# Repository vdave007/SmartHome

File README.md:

# SmartHome
Smart Home -hardware and backend

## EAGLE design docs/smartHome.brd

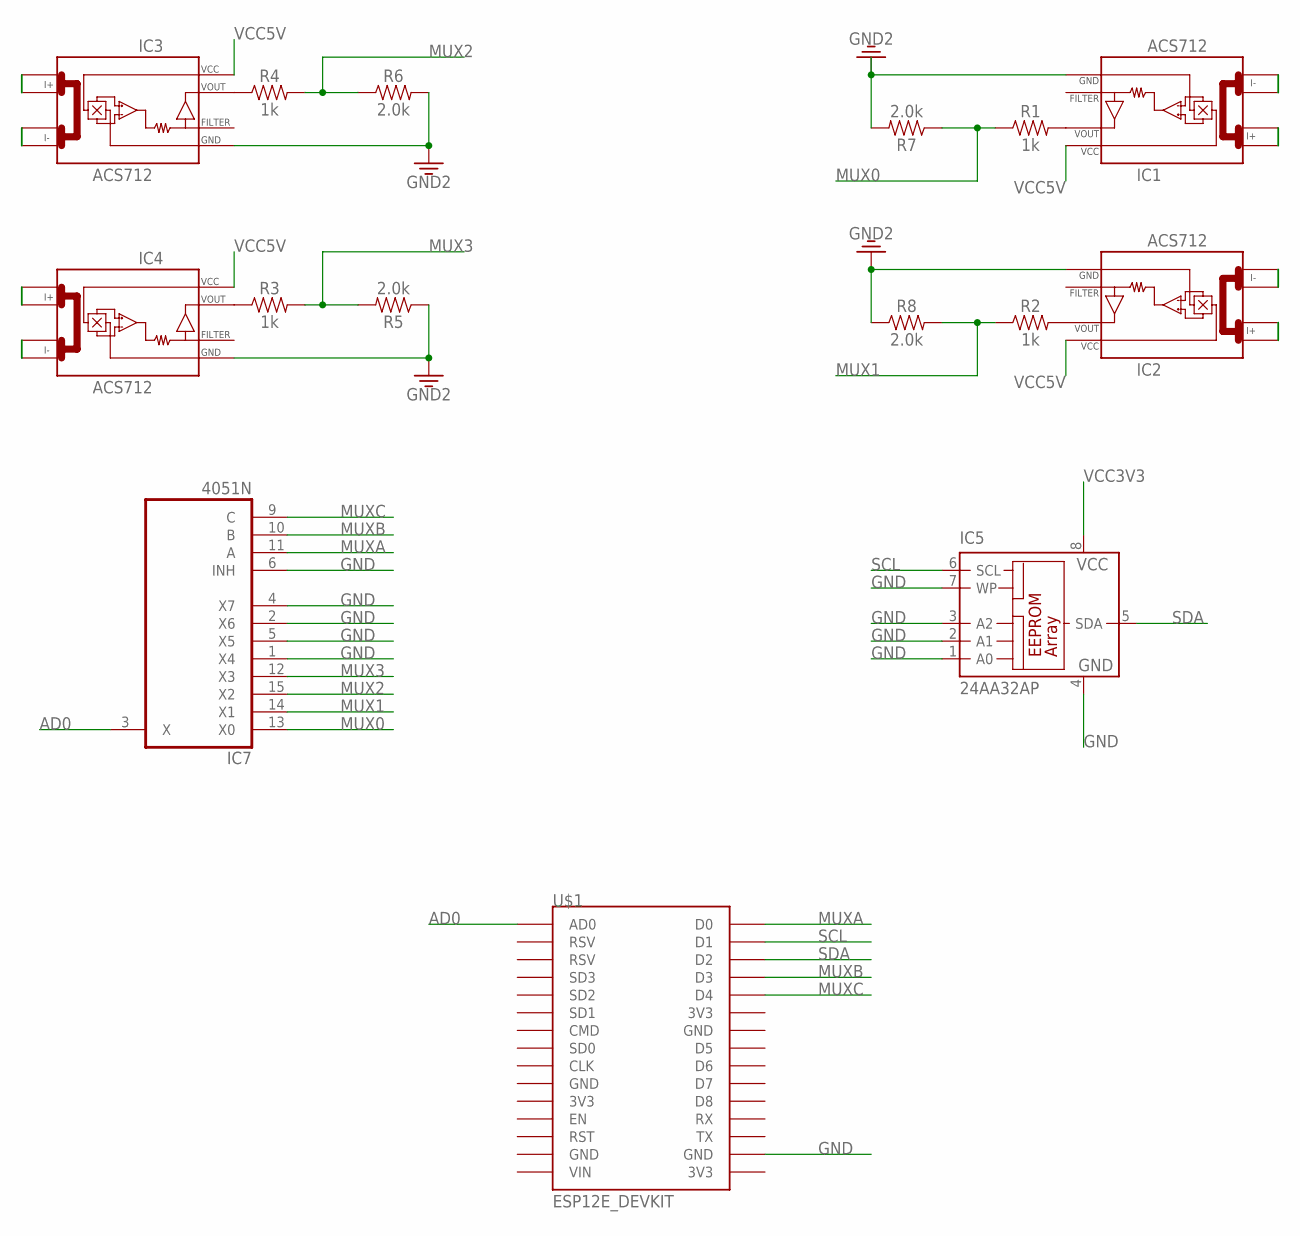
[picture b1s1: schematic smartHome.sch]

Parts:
IC1, IC2, IC3, IC4: ACS712; SO08
IC5: 24AA32AP; DIL8
IC7: 4051N; DIL16
R1, R2, R3, R4: 1k; AXIAL-0.3
R5, R6, R7, R8: 2.0k; 0603
U$1: ESP12E_DEVKIT

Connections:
AD0: IC7.3 (X), U$1.AD0
GND: IC1.5 (GND), IC2.5 (GND), IC3.5 (GND), IC4.5 (GND), IC5.1 (A0), IC5.2 (A1), IC5.3 (A2), IC5.4 (GND), IC5.7 (WP), IC7.1 (X4), IC7.2 (X6), IC7.4 (X7), IC7.5 (X5), IC7.6 (INH), IC7.8 (GND), R5.1, R6.2, R7.2, R8.1, U$1.GND@3 (GND)
MUX0: IC7.13 (X0), R1.P$1 (1), R7.1
MUX1: IC7.14 (X1), R2.P$1 (1), R8.2
MUX2: IC7.15 (X2), R4.P$2 (2), R6.1
MUX3: IC7.12 (X3), R3.P$2 (2), R5.2
MUXA: IC7.11 (A), U$1.D0
MUXB: IC7.10 (B), U$1.D3
MUXC: IC7.9 (C), U$1.D4
unnamed: IC1.7 (VOUT), R1.P$2 (2)
unnamed: IC2.7 (VOUT), R2.P$2 (2)
unnamed: IC3.7 (VOUT), R4.P$1 (1)
unnamed: IC4.7 (VOUT), R3.P$1 (1)
SCL: IC5.6 (SCL), U$1.D1
SDA: IC5.5 (SDA), U$1.D2
VCC: IC7.16 (VCC)
VCC3V3: IC5.8 (VCC)
VCC5V: IC1.8 (VCC), IC2.8 (VCC), IC3.8 (VCC), IC4.8 (VCC)
VEE: IC7.7 (VEE)

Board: 2 copper layers, 15 parts (0 on the bottom side), 16 nets, no tracks yet.

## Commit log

2017-01-04 Skeleton for the backend. Very primitive yet.
2017-01-04 Added mongoose implementation
2017-01-04 Added API for hardware to post his raw data
2017-02-07 Added communication: backend-hardware
2017-02-20 Corrected some errors so it works on cloud to
    *Added "use strict"
2017-02-20 Rewrote the code so now its more OOP and uses PlatformIO
2017-02-21 Added Acs712 and NetworkController classes
    * !Untested on device
2017-02-27 Added EEPROM class *UNTESTED!
2017-03-05 Tested on device!
2017-03-06 Corrected getACRMS function
2017-03-24 added backend for android
2017-03-24 it need to be int watt value
2017-03-25 Config store and new eeprom implementation... MUST FINISH
2017-03-26 Implemented some configstor, still needs changes.
2017-03-27 added original_value for fix the devicesetting bug
2017-04-01 mesages refactored to boolean
2017-04-02 Corrected EEPROM and now reports with good device ID
2017-04-02 Implemented ConfigStore Save
2017-04-03 Revolutionary measurement!
2017-04-10 Added Eagle-file for SmartHome+NodeMCU
2017-04-10 Rewrote to POST
2017-04-10 added body parser
2017-04-11 added socket
2017-04-11 notification sender
2017-04-17 Started implementing eepromInitializer with config page. Get method added to networkController
2017-05-15 Added support for WeMoS D1
2017-05-19 added socket for notification
2017-05-31 Added Docker support for the backend.
2017-06-01 Quickfix in docker file
2017-06-01 gethousesbyid method added
2017-06-02 Created the configpage for the device
    *Pin D5 must be pulled HIGH for the device to enter config-mode
    *When in config mode you access the device on the 192.168.4.1 IP
    *Wifi and backend can be configured here
2017-06-02 Small fix - changed saving method for backend ip
2017-06-03 Fixed eeprom configuration save issue
2017-06-03 Added custom structure that keeps the last X number of measured current on the given cID
2017-06-03 Modified docker-compose file so it will work on AWS
2017-06-03 Corrected typo
2017-06-03 Fixed Eeprom write if you get smaller string after bigger
2017-06-04 id type changed to string
2017-06-07 valuedelay added
2017-06-08 Quickfix for FirstRun
2017-06-08 added mailer for sending reset password mails
2017-06-24 added model for resetpassword to save in db
2017-06-25 sms service added
2017-06-25 changed sms sending
2017-06-26 Created AI for deciding the curent devices in use.
    Currently still unimplemented, only the skeleton for it.
    Rewrote the routes so it will use the new class.
2017-06-28 Added class for keeping track of currently used devices
2017-06-29 Added Led functions for the device
2017-06-29 Backend can now decide if a device has been turned on/off
    Added new route to get the currently working devices
    Changed the new api in device configuration
2017-06-29 added models from development-Akos
2017-06-29 new modules added to package.json
2017-06-29 merged with development-Akos
2017-06-29 new Class for deciding devices identity
2017-06-29 added new dependencies for Encryptation , Mail, Sms, DeviceSelector
2017-06-29 merged to database.js
2017-06-29 email changed
2017-06-29 api routh path added
2017-06-29 added socket.js for android notification
2017-06-29 mock for testing app without microcontroller device
2017-06-29 api route
2017-06-29 changed db to database in 1 route
2017-06-29 needed to add use strict
2017-07-01 Small fixes for removing and coloring
2017-07-01 add house fix
2017-07-03 fixed house adding - and implemented selector for ai returned devices
2017-07-04 Small fix in decision making on backend
2017-07-04 Removed a braclet
2017-07-04 SmallFix on removing devices
2017-07-04 Fixed a typo
2017-07-04 Fixed equation in decision algorithm
2017-07-05 Fixed Removing Algorithm

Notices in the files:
parts and their libraries:
SparkFun-Resistors: Licensing: Creative Commons ShareAlike 4.0 International - https://creativecommons.org/licenses/by-sa/4.0
